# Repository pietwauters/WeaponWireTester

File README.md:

# WeaponWireTester

**ESP32-based weapon & wire tester for fencing** — zero-button UX, fast fault finding, and accurate resistance measurement.  
Supports **body cords** and **weapons** (foil, sabre, épée). Lamé continuity is **WIP**.

---

## Overview

- **Auto mode detection:** No buttons. The tester watches the connectors and switches between **wire test** and **weapon test** automatically.  
- **Intermittent fault capture:** Brief dropouts are latched and displayed for a few seconds.  
- **Clear LED UI:** 5×5 WS2812B matrix with intuitive color/status cues.  
- **Power:** USB-C (power bank or USB adapter).

**Connections:**  
- Plug the **enrouleur-side** body-cord plug into the **right** side of the tester, and the **weapon-side** plug into the **left** side.  
- A small hole accommodates the **foil/sabre safety clip**.  
- A small **lamé patch** on the enclosure allows clipping the crocodile clip.

*(Power via USB-C)*

---

## Quick start

1. **Power on** via USB-C.  
2. **Connect** a body cord on both sides, or a cord + weapon; the tester selects the mode automatically.  
3. **Wiggle-test** connectors and cable to expose intermittent faults (they’ll be latched briefly).

---

## Operation

### Mode selection (automatic)
- A detected connection **between cord pins** → **Wire Test**.  
- A **cord + weapon** combination → **Weapon Test** (foil/sabre/épée detected by wiring).

### Wire testing

**Two phases:**

1) **Quick Check** — Fast screening for obvious problems (broken wires, swaps, shorts). An animation highlights faults right-to-left / bottom-to-top.  
2) **Accurate Resistance** — Fine measurement; color encodes ohmic range. Move the cable/plug to catch intermittents.

| Display cue        | Meaning                                  | Resistance (Ω)     |
|--------------------|-------------------------------------------|--------------------|
| **Green solid**     | Good connection                           | **< 3**            |
| **Yellow solid**    | Acceptable / watchlist                    | **3 – 5**          |
| **Red solid**       | Out of spec (may still “work” sometimes)  | **5 – 10**         |
| **Red dotted**      | Broken / open                             | **> 10**           |
| **Blue**            | Unintended short between lines            | —                  |

### Weapon testing

**Foil & Sabre**
- **Idle:** No lights.  
- **Point pressed / intermittent on either wire:** **White** latched for a few seconds.  
- **Point pressed on lamé:** **Green** (valid touch).

**Épée**
- **Point pressed:** **Green** (valid touch).  
- **Any wire-to-wire short:** **Blue**.

---

## Hardware

- **Enclosure (3D print):** https://www.printables.com/model/1006755-body-wire-weapon-test-box  
  Brass inserts used: **M2** (PCB) and **M6** (lamé patch).  
- **Display:** 5×5 **WS2812B** LED matrix (mounted to top panel).  
- **Main PCB:** shared with the [3-weapon scoring device](https://github.com/pietwauters/esp32_scoring_device_hardware).

---

## Availability (dev leftovers)

From time to time we may have **bare PCBs**, **populated PCBs**, or **complete kits** available from development batches.  
If you’re interested, **please contact us privately** (do **not** post personal details in public issues):

- 📧 **colloid-nougat-42@icloud.com**

Stock is limited and irregular; first-come, first-served.

---

## Project status / roadmap

- ✅ Body-cord testing (auto detect, quick + accurate modes)  
- ✅ Weapon testing (foil/sabre/épée)  
- 🛠️ Lamé continuity test (**in progress**)  

Contributions welcome — see `CONTRIBUTING.md`.

---

## Licensing

- **Software:** Apache-2.0  
- **Hardware designs & docs:** **CC BY-NC-SA 4.0** (remix allowed; attribution + share-alike; **non-commercial**)  
- **Commercial use:** available by agreement — see `COMMERCIAL-LICENSING.md`.  
  - Policy: producing **> 10 units** total (including remixes/derivatives), whether sold or given away, is **commercial**.

**Attribution example:**  
“Based on *WeaponWireTester* by **Piet Wauters & Claude Wolter**, licensed CC BY-NC-SA 4.0.”

---

## Safety note

This tester is **not** for mains/line-voltage use. Use only with fencing equipment and follow your federation’s safety rules.

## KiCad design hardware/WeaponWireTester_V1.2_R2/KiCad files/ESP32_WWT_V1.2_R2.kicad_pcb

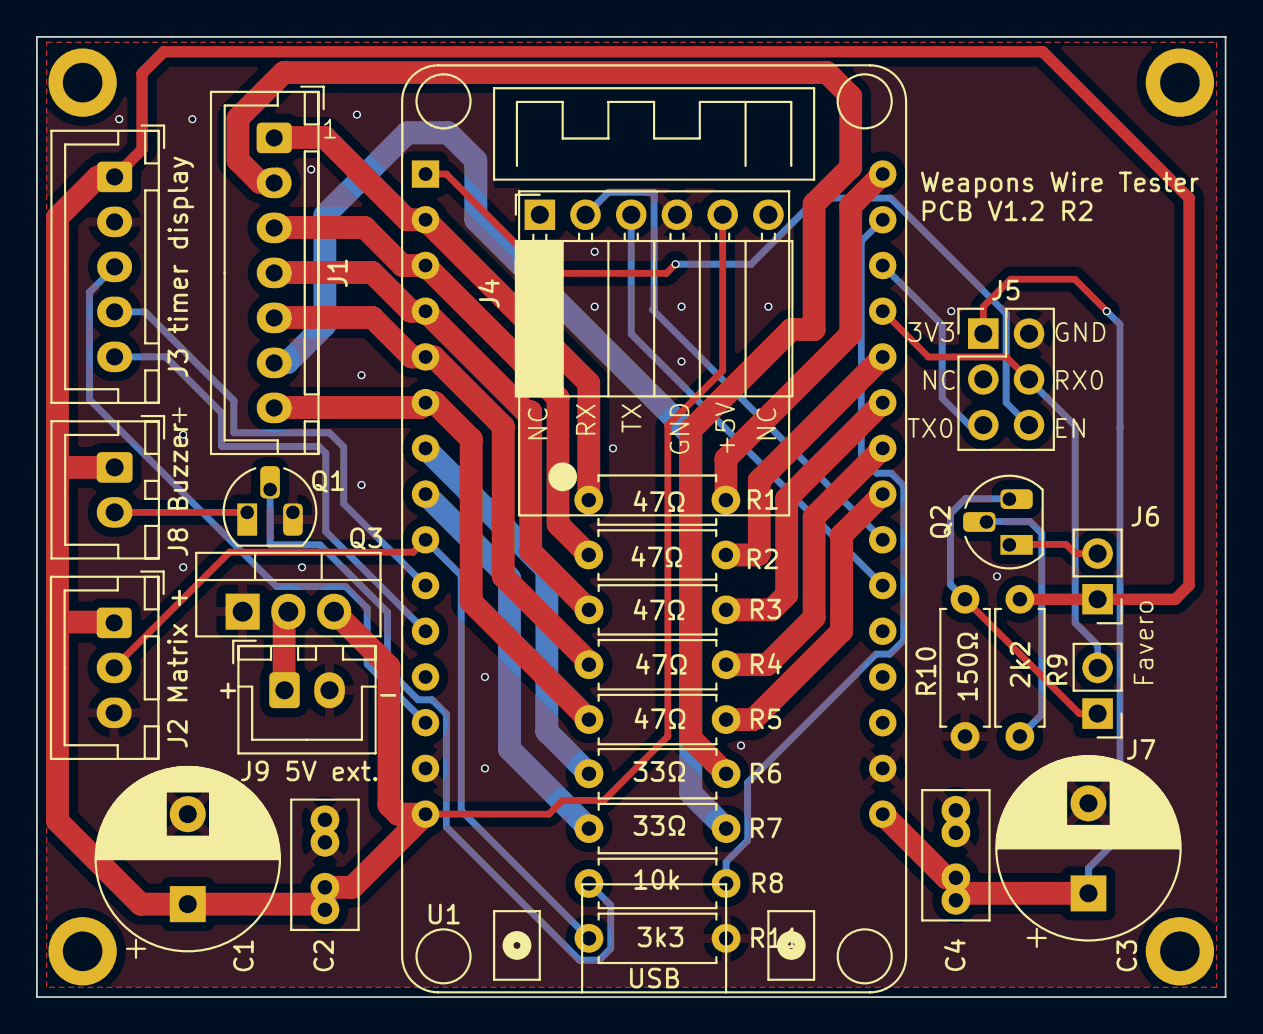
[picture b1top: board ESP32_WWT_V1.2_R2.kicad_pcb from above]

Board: 2 copper layers, 66.0 x 53.3 mm, 32 parts (0 on the bottom side), 33 nets.

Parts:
C1, C3: 470µF; CP_Radial_D10.0mm_P5.00mm
C2, C4: 100nF; C_Rect_L7.0mm_W3.5mm_P2.50mm_P5.00mm
H1, H2, H3, H4: MountingHole_2.2mm_M2_DIN965_Pad
J1: Fencers; JST_XH_B7B-XH-A_1x07_P2.50mm_Vertical
J2 Matrix +: WS2812B LED Matrix; JST_XH_B3B-XH-A_1x03_P2.50mm_Vertical
J3 timer display: MAX7219 Timer Display; JST_XH_B5B-XH-A_1x05_P2.50mm_Vertical
J4: HC-06 BT module; PinSocket_1x06_P2.54mm_Horizontal
J5: ICSP; PinHeader_2x03_P2.54mm_Vertical
J6, J7: Conn_01x02; PinHeader_1x02_P2.54mm_Vertical
J8 Buzzer: Buzzer; JST_XH_B2B-XH-A_1x02_P2.50mm_Vertical
J9 5V ext.: 5V ext. Power; JST_XH_B2B-XH-A_1x02_P2.50mm_Vertical
Q1, Q2: BC337; TO-92L_HandSolder
Q3: FQP27P06; TO-220-3_Vertical
R1, R2, R3, R4, R5: 47Ω; R_Axial_DIN0207_L6.3mm_D2.5mm_P7.62mm_Horizontal
R6, R7: 33Ω; R_Axial_DIN0207_L6.3mm_D2.5mm_P7.62mm_Horizontal
R8: 3k3; R_Axial_DIN0207_L6.3mm_D2.5mm_P7.62mm_Horizontal
R9: 2k2; R_Axial_DIN0207_L6.3mm_D2.5mm_P7.62mm_Horizontal
R10: 150Ω; R_Axial_DIN0207_L6.3mm_D2.5mm_P7.62mm_Horizontal
R11: 10k; R_Axial_DIN0207_L6.3mm_D2.5mm_P7.62mm_Horizontal
U1: ESP32_DevKit_V1_DOIT 30pin; esp32_devkit_v1_doit

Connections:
+3.3V: C3.1, C4.1, J5.1, U1.16 (3V3)
+5V: C1.1, C2.1, J2 Matrix +.1, J3 timer display.1, J4.5, J6.1, J8 Buzzer.1, Q3.3 (S), R9.2, U1.15 (VIN)
GND: C1.2, C2.2, C3.2, C4.2, J2 Matrix +.3, J3 timer display.2, J4.4, J5.2, J9 5V ext..2, Q1.3 (E), Q3.1 (G), R10.2, R11.2, U1.14 (GND), U1.17 (GND)
unnamed: J1.1, R1.2, U1.2 (SENSOR_VP)
unnamed: J1.2, R6.2
unnamed: J1.3, R2.1, U1.3 (SENSOR_VN)
unnamed: J1.4, R3.2, U1.4 (IO34)
unnamed: J1.5, R4.2, U1.5 (IO35)
unnamed: J1.6, R7.2
unnamed: J1.7, R5.2, U1.6 (IO32)
unnamed: J2 Matrix +.2, R11.1, U1.9 (IO26)
unnamed: J3 timer display.3, U1.13 (IO13)
unnamed: J3 timer display.4, U1.10 (IO27)
unnamed: J3 timer display.5, U1.11 (IO14)
unnamed: J4.2, U1.22 (IO17)
unnamed: J4.3, U1.21 (IO16)
unnamed: J5.4, J7.2, U1.27 (RXD0/IO3)
unnamed: J5.5, U1.28 (TXD0/IO1)
unnamed: J5.6, U1.1 (EN)
unnamed: J6.2, Q2.1 (C)
unnamed: J7.1, Q2.3 (E), R10.1
unnamed: J8 Buzzer.2, Q1.1 (C)
unnamed: J9 5V ext..1, Q3.2 (D)
unnamed: Q1.2 (B), R8.1
unnamed: Q2.2 (B), R9.1
unnamed: R5.1, U1.23 (IO5)
unnamed: R4.1, U1.24 (IO18)
unnamed: R3.1, U1.25 (IO19)
unnamed: R2.2, U1.26 (IO21)
unnamed: R8.2, U1.29 (IO22)
unnamed: R1.1, U1.30 (IO23)
unnamed: R7.1, U1.8 (IO25)
unnamed: R6.1, U1.7 (IO33)

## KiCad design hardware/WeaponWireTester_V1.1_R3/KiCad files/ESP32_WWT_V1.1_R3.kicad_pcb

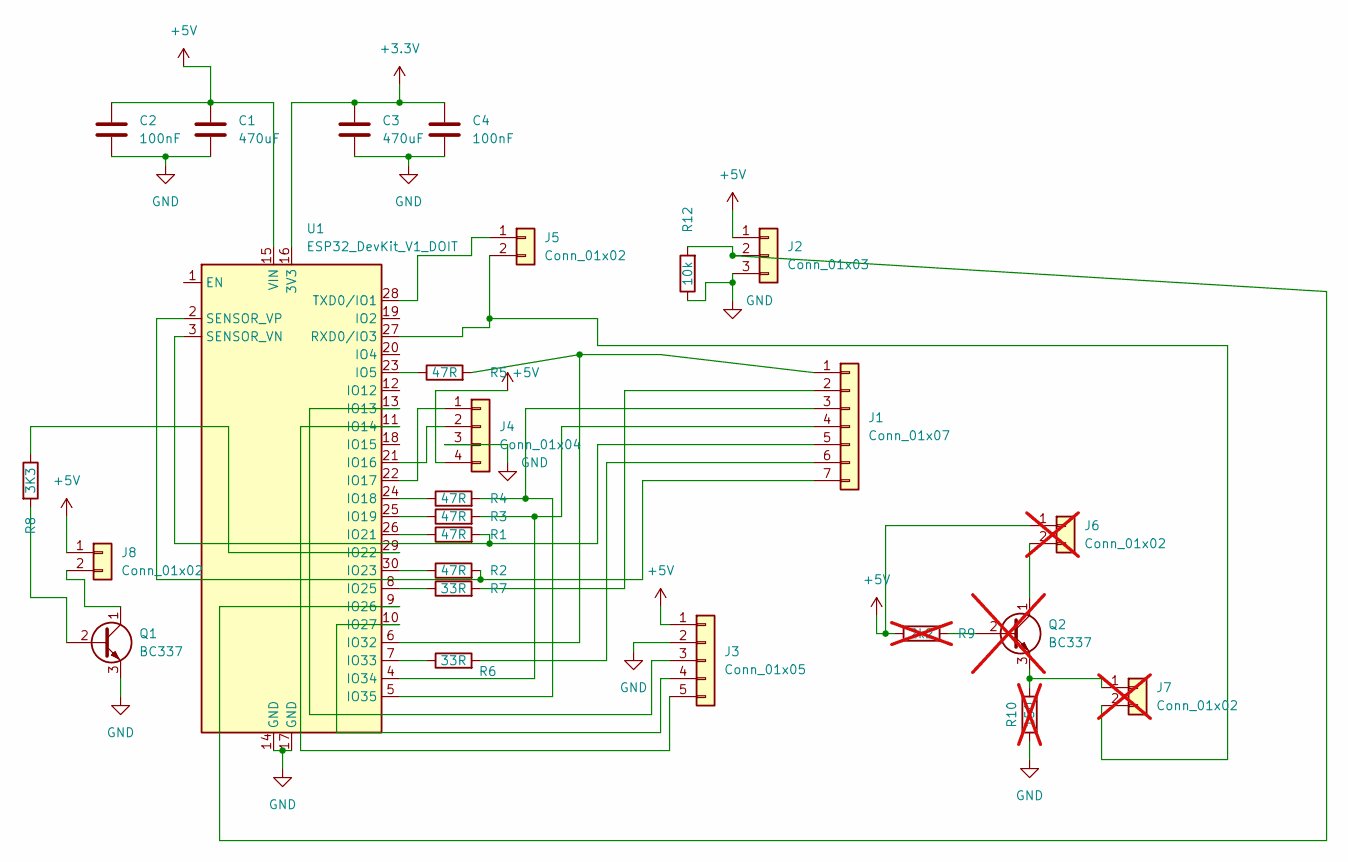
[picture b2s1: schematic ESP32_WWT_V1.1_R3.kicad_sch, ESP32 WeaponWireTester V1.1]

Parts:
C1, C3: 470uF; CP_Radial_D10.0mm_P5.00mm
C2, C4: 100nF; C_Rect_L7.2mm_W2.5mm_P5.00mm_FKS2_FKP2_MKS2_MKP2
J1: Conn_01x07; PinHeader_1x07_P2.54mm_Vertical
J2: Conn_01x03; PinHeader_1x03_P2.54mm_Vertical
J3: Conn_01x05; PinHeader_1x05_P2.54mm_Vertical
J4: Conn_01x04; PinHeader_1x04_P2.54mm_Vertical
J5, J8: Conn_01x02; PinHeader_1x02_P2.54mm_Vertical
J6, J7: Conn_01x02; PinHeader_1x02_P2.54mm_Vertical; not fitted
Q1: BC337; TO-92L_HandSolder
Q2: BC337; TO-92L_HandSolder; not fitted
R1, R2, R3, R4, R5: 47R; R_Axial_DIN0207_L6.3mm_D2.5mm_P10.16mm_Horizontal
R6, R7: 33R; R_Axial_DIN0207_L6.3mm_D2.5mm_P10.16mm_Horizontal
R8: 3K3; R_Axial_DIN0207_L6.3mm_D2.5mm_P10.16mm_Horizontal
R9: 2k2; R_Axial_DIN0207_L6.3mm_D2.5mm_P10.16mm_Horizontal; not fitted
R10: 150; R_Axial_DIN0207_L6.3mm_D2.5mm_P10.16mm_Horizontal; not fitted
R12: 10k; R_Axial_DIN0207_L6.3mm_D2.5mm_P10.16mm_Horizontal
U1: ESP32_DevKit_V1_DOIT; esp32_devkit_v1_doit

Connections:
+3.3V: C3.1, C4.1, U1.16 (3V3)
+5V: C1.1, C2.1, J2.1, J3.1, J4.4, J6.1, J8.1, R9.1, U1.15 (VIN)
GND: C1.2, C2.2, C3.2, C4.2, J2.3, J3.2, J4.3, Q1.3 (E), R10.2, R12.1, U1.14 (GND), U1.17 (GND)
unnamed: J1.1, R5.2, U1.6 (IO32)
unnamed: J1.2, R7.2
unnamed: J1.3, R4.2, U1.5 (IO35)
unnamed: J1.4, R3.2, U1.4 (IO34)
unnamed: J1.5, R1.2, U1.3 (SENSOR_VN)
unnamed: J1.6, R6.2
unnamed: J1.7, R2.2, U1.2 (SENSOR_VP)
unnamed: J2.2, R12.2, U1.9 (IO26)
unnamed: J3.3, U1.13 (IO13)
unnamed: J3.4, U1.10 (IO27)
unnamed: J3.5, U1.11 (IO14)
unnamed: J4.1, U1.22 (IO17)
unnamed: J4.2, U1.21 (IO16)
unnamed: J5.1, U1.28 (TXD0/IO1)
unnamed: J5.2, J7.2, U1.27 (RXD0/IO3)
unnamed: J6.2, Q2.1 (C)
unnamed: J7.1, Q2.3 (E), R10.1
unnamed: J8.2, Q1.1 (C)
unnamed: Q1.2 (B), R8.2
unnamed: Q2.2 (B), R9.2
unnamed: R5.1, U1.23 (IO5)
unnamed: R4.1, U1.24 (IO18)
unnamed: R3.1, U1.25 (IO19)
unnamed: R1.1, U1.26 (IO21)
unnamed: R8.1, U1.29 (IO22)
unnamed: R2.1, U1.30 (IO23)
unnamed: R7.1, U1.8 (IO25)
unnamed: R6.1, U1.7 (IO33)

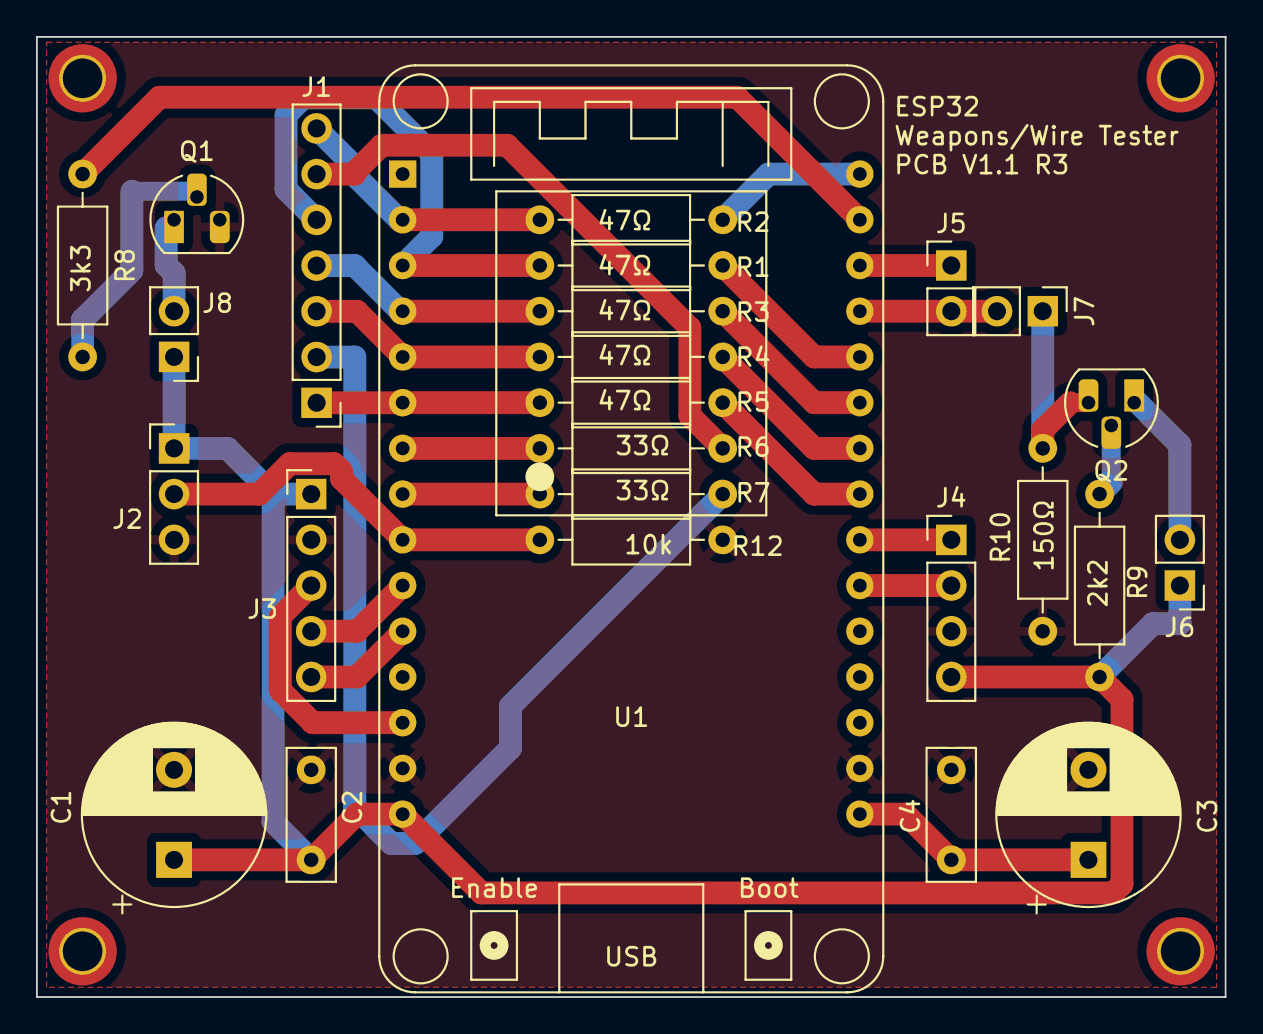
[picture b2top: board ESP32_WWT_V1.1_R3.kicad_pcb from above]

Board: 2 copper layers, 66.0 x 53.3 mm, 30 parts (0 on the bottom side), 31 nets.

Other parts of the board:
HOLE1, HOLE2, HOLE3, HOLE4: MountingHole_2.2mm_M2_DIN965_Pad_TopBottom

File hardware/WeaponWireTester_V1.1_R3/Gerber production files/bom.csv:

Designator,Footprint,Quantity,Value,LCSC Part #
"C1, C3",CP_Radial_D10.0mm_P5.00mm,2,470uF,
"C2, C4",C_Rect_L7.2mm_W2.5mm_P5.00mm_FKS2_FKP2_MKS2_MKP2,2,100nF,
"HOLE1, HOLE2, HOLE3, HOLE4",MountingHole_2.2mm_M2_DIN965_Pad_TopBottom,4,MountingHole_2.2mm_M2_DIN965_Pad_TopBottom,
J1,PinHeader_1x07_P2.54mm_Vertical,1,Conn_01x07,
J2,PinHeader_1x03_P2.54mm_Vertical,1,Conn_01x03,
J3,PinHeader_1x05_P2.54mm_Vertical,1,Conn_01x05,
J4,PinHeader_1x04_P2.54mm_Vertical,1,Conn_01x04,
"J5, J8",PinHeader_1x02_P2.54mm_Vertical,2,Conn_01x02,
Q1,TO-92L_HandSolder,1,BC337,
"R1, R2, R3, R4, R5",R_Axial_DIN0207_L6.3mm_D2.5mm_P10.16mm_Horizontal,5,47R,
R12,R_Axial_DIN0207_L6.3mm_D2.5mm_P10.16mm_Horizontal,1,10k,
"R6, R7",R_Axial_DIN0207_L6.3mm_D2.5mm_P10.16mm_Horizontal,2,33R,
R8,R_Axial_DIN0207_L6.3mm_D2.5mm_P10.16mm_Horizontal,1,3K3,
U1,esp32_devkit_v1_doit,1,ESP32_DevKit_V1_DOIT,

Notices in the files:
hardware/WeaponWireTester_V1.1_R3/KiCad files/ESP32_WWT_V1.1_R3.kicad_pcb:
©2025  CC BY-NC-SA 4.0
©Piet Wauters 2024 GNU GPL V3.0
hardware/WeaponWireTester_V1.2_R2/KiCad files/ESP32_WWT_V1.2_R2.kicad_pcb:
©2024-25 CC BY-NC-SA 4.0 NC>10 units = commercial
